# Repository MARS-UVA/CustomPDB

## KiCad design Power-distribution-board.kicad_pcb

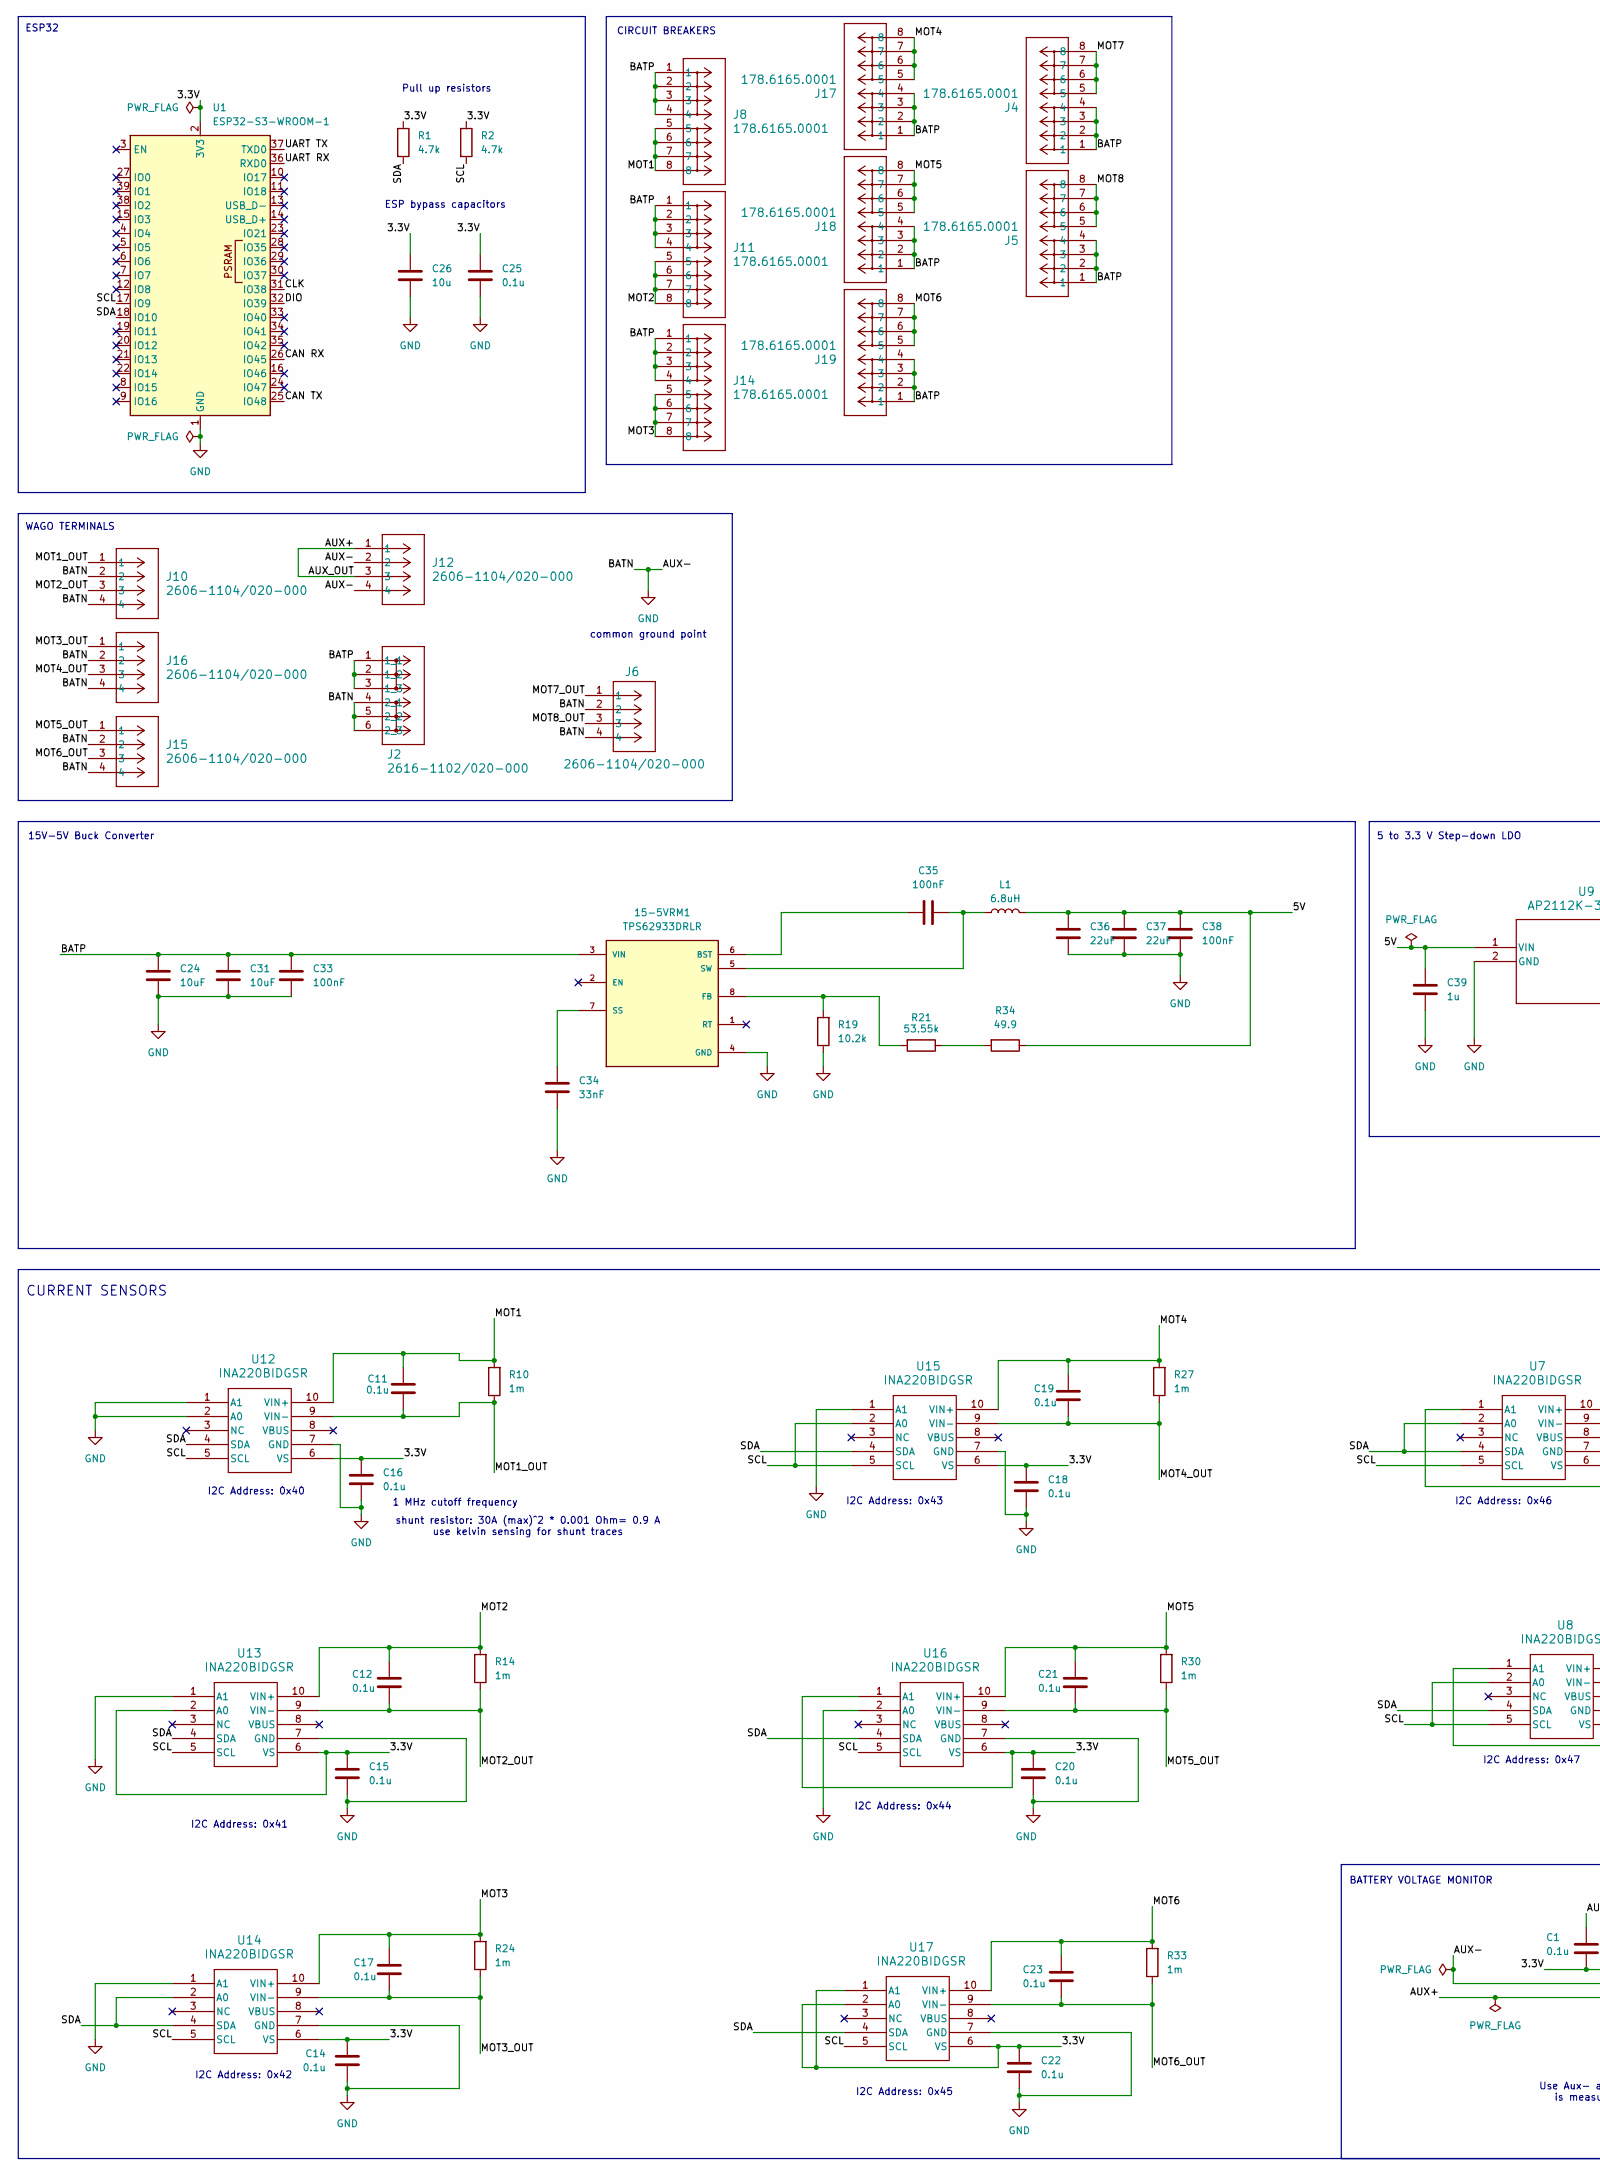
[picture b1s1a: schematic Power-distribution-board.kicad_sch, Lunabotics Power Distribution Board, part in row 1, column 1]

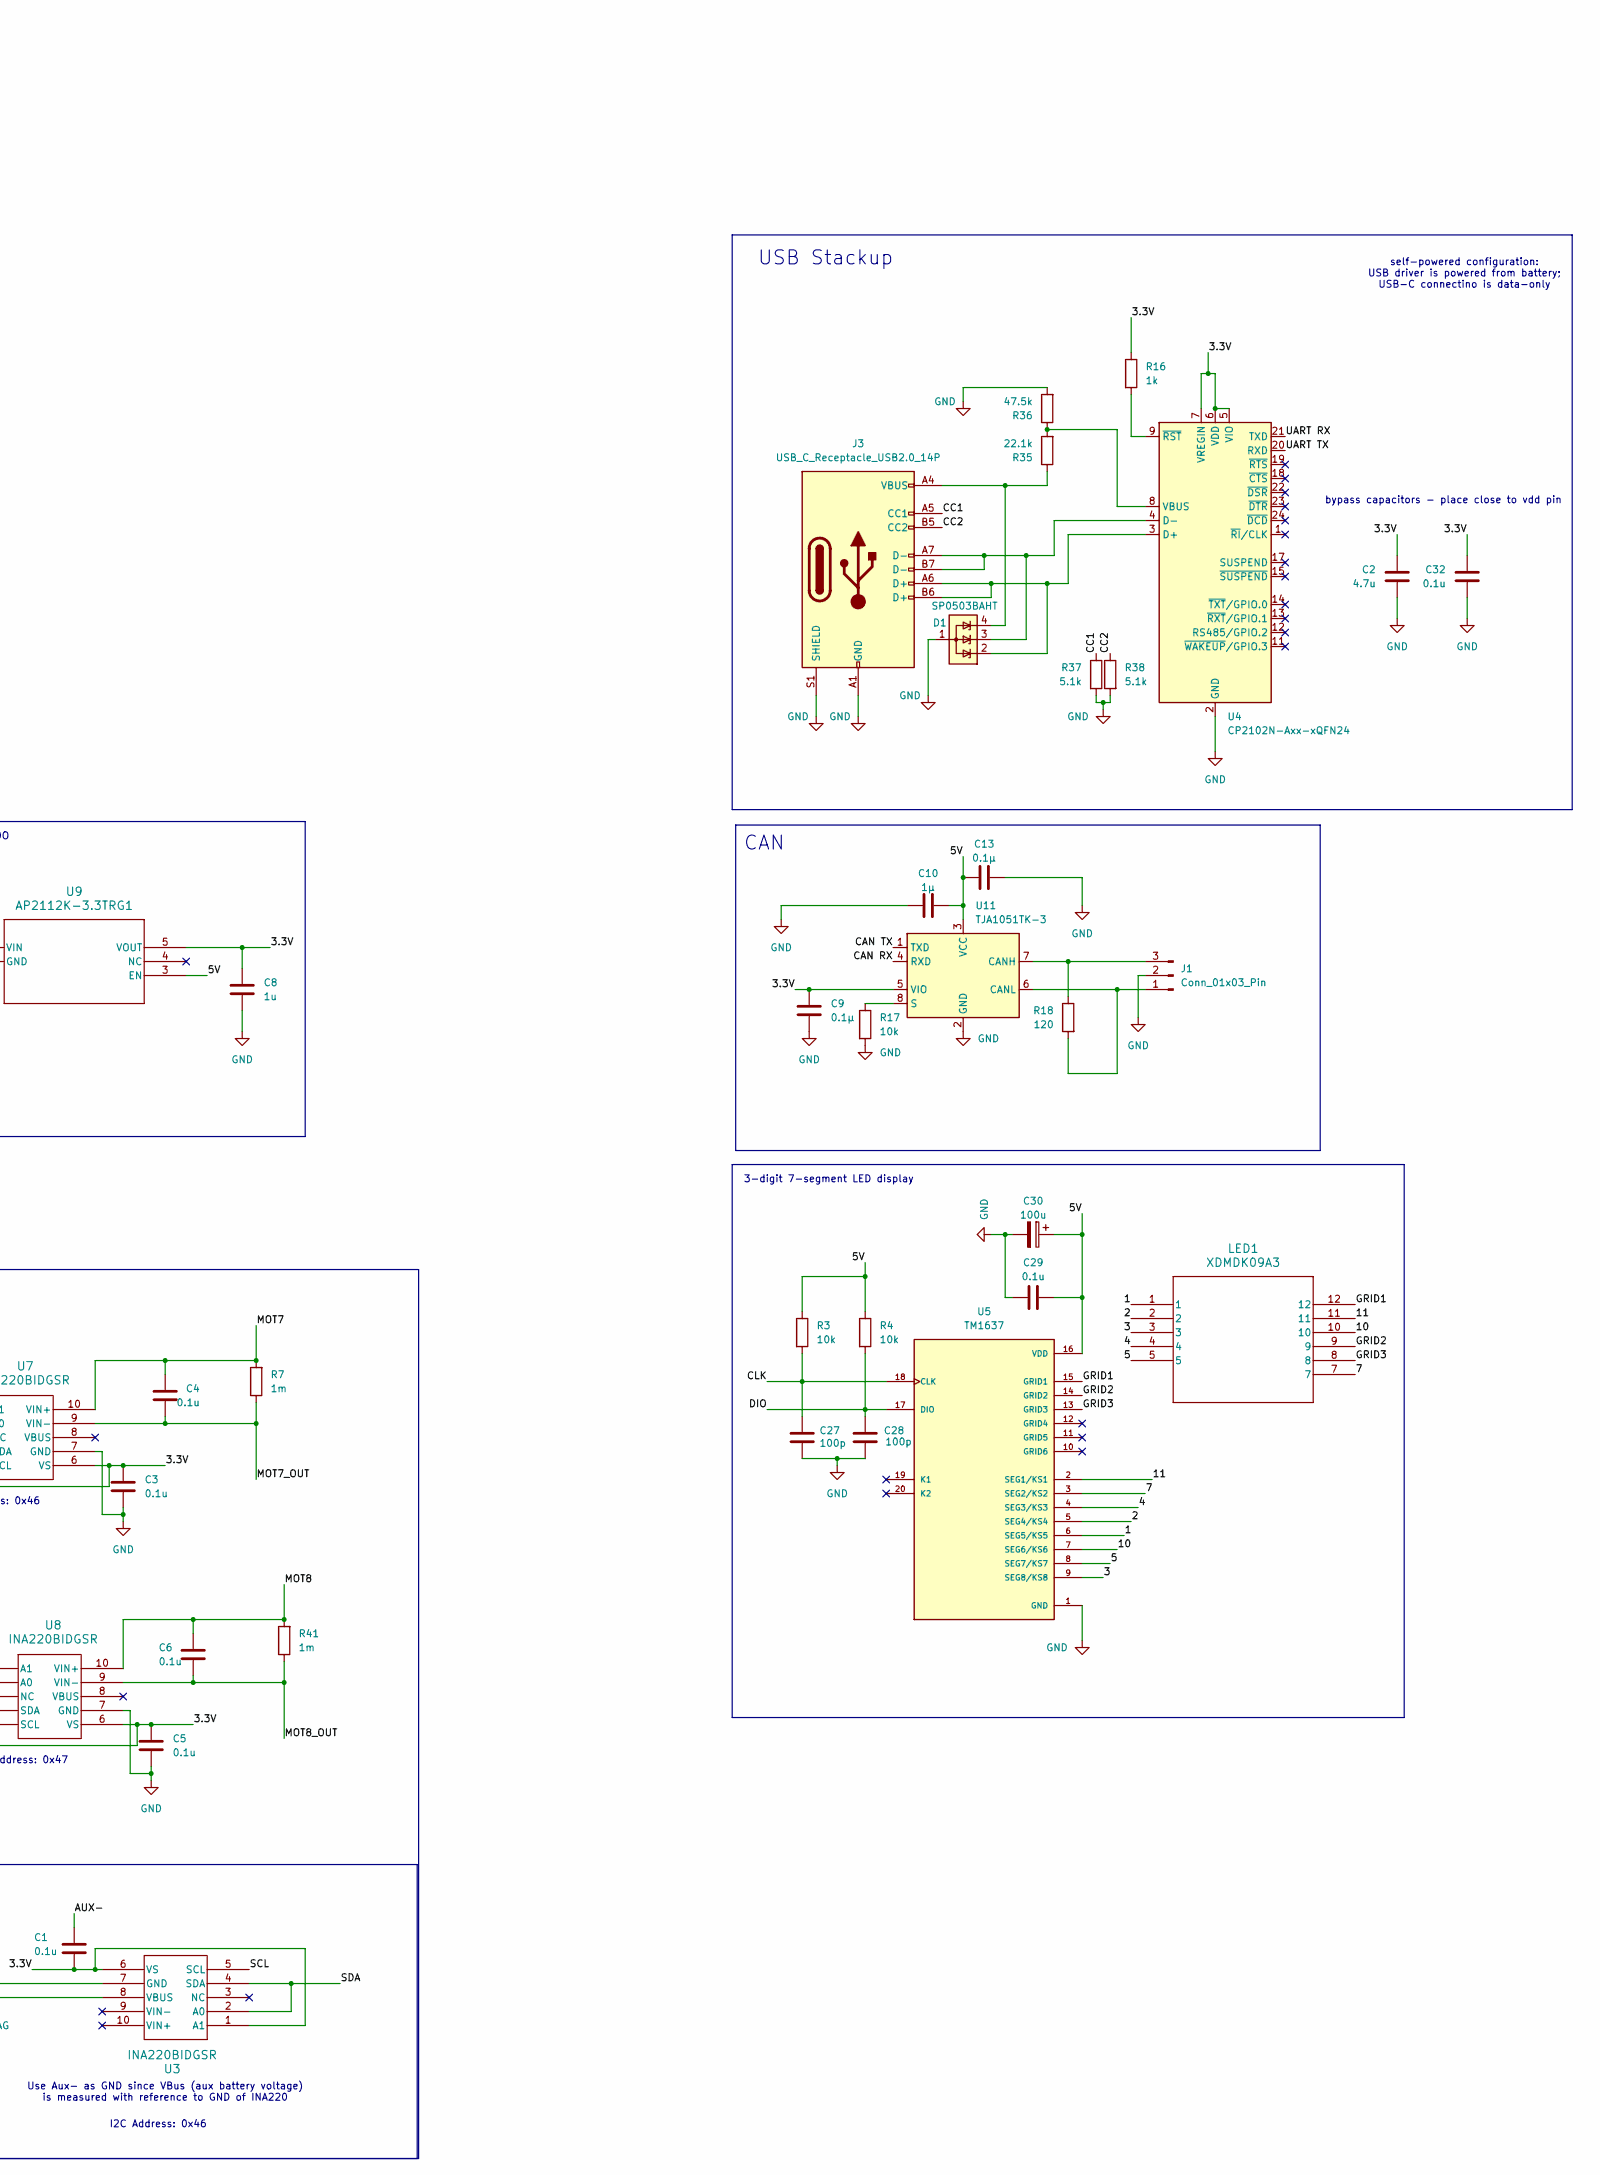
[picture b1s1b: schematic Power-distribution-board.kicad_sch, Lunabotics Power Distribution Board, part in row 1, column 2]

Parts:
15-5VRM1: TPS62933DRLR; SOT-5X3-8_DRL_TEX; PARTREV D
C1, C3, C4, C5, C6, C11, C12, C14, C15, C16, C17, C18, C19, C20, C21, C22, C23, C25, C29, C32: 0.1u; R_0805_2012Metric
C2: 4.7u; C_0805_2012Metric
C8, C39: 1u; C_0805_2012Metric
C9, C13: 0.1µ; C_0805_2012Metric
C10: 1µ; C_0805_2012Metric
C24, C31: 10uF; CAP_CGA5_TDK-M
C26: 10u; C_0805_2012Metric
C27, C28: 100p; C_0805_2012Metric
C30: 100u; CP_Elec_3x5.4
C33, C35, C38: 100nF; C_0805_2012Metric
C34: 33nF; C_0805_2012Metric
C36, C37: 22uF; C_0805_2012Metric
D1: SP0503BAHT; SOT-143
J1: Conn_01x03_Pin; Molex_Micro-Fit_3.0_43650-0300_1x03_P3.00mm_Horizontal
J2: 2616-1102/020-000; CONN2_2616-1102&slash_020-000_WAG
J3: USB_C_Receptacle_USB2.0_14P; USB_C_Receptacle_HRO_TYPE-C-31-M-12
J4, J5, J8, J11, J14, J17, J18, J19: 178.6165.0001; CONN_178.6165.0001_LTF
J6, J10, J12, J15, J16: 2606-1104/020-000; CONN4_2606-1104&slash_020-000_WAG
L1: 6.8uH; L_Wuerth_XHMI-6060
LED1: XDMDK09A3; XDMDK09A3_SLD
R1, R2: 4.7k; R_0402_1005Metric
R3, R4, R17: 10k; R_0402_1005Metric
R7, R10, R14, R24, R27, R30, R33, R41: 1m; RES_3920R_1L00x_BRN-M
R16: 1k; R_0402_1005Metric
R18: 120; R_0402_1005Metric
R19: 10.2k; R_0805_2012Metric
R21: 53.55k; R_0805_2012Metric
R34: 49.9; R_0805_2012Metric
R35: 22.1k; R_0402_1005Metric
R36: 47.5k; R_0402_1005Metric
R37, R38: 5.1k; R_0402_1005Metric
U1: ESP32-S3-WROOM-1
U3, U7, U8, U12, U13, U14, U15, U16, U17: INA220BIDGSR; DGS10
U4: CP2102N-Axx-xQFN24; QFN-24-1EP_4x4mm_P0.5mm_EP2.6x2.6mm
U5: TM1637; LED_driver_DIP778W43P254L2612H431Q20N; PARTREV v2.5
U9: AP2112K-3.3TRG1; SOT_RG1_DIO
U11: TJA1051TK-3; HVSON-8-1EP_3x3mm_P0.65mm_EP1.6x2.4mm

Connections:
/1: LED1.1, U5.6 (SEG5/KS5)
/2: LED1.2, U5.5 (SEG4/KS4)
/3: LED1.3, U5.9 (SEG8/KS8)
/3.3V: C1.1, C2.2, C3.1, C5.1, C8.1, C9.2, C14.1, C15.1, C16.1, C18.1, C20.1, C22.1, C25.2, C26.2, C32.2, R1.1, R2.1, R16.1, U1.2 (3V3), U3.1 (A1), U3.6 (VS), U4.5 (VIO), U4.6 (VDD), U4.7 (VREGIN), U7.1 (A1), U7.6 (VS), U8.1 (A1), U8.6 (VS), U9.5 (VOUT), U11.5 (VIO), U12.6 (VS), U13.2 (A0), U13.6 (VS), U14.6 (VS), U15.6 (VS), U16.1 (A1), U16.6 (VS), U17.1 (A1), U17.2 (A0), U17.6 (VS)
/4: LED1.4, U5.4 (SEG3/KS3)
/5: LED1.5, U5.8 (SEG7/KS7)
/5V: C10.2, C13.1, C29.2, C30.1, C36.1, C37.1, C38.1, C39.1, L1.2, R3.1, R4.1, R34.1, U5.16 (VDD), U9.1 (VIN), U9.3 (EN), U11.3 (VCC)
/7: LED1.7, U5.3 (SEG2/KS2)
/10: LED1.10, U5.7 (SEG6/KS6)
/11: LED1.11, U5.2 (SEG1/KS1)
/AUX+: J12.1, J12.3, U3.8 (VBUS)
/BATP: 15-5VRM1.3 (VIN), C24.1, C31.1, C33.1, J2.1 (1_1), J2.2 (1_2), J2.3 (1_3), J4.1, J4.2, J4.3, J4.4, J5.1, J5.2, J5.3, J5.4, J8.1, J8.2, J8.3, J8.4, J11.1, J11.2, J11.3, J11.4, J14.1, J14.2, J14.3, J14.4, J17.1, J17.2, J17.3, J17.4, J18.1, J18.2, J18.3, J18.4, J19.1, J19.2, J19.3, J19.4
/CAN RX: U1.26 (IO45), U11.4 (RXD)
/CAN TX: U1.25 (IO48), U11.1 (TXD)
/CC1: J3.A5 (CC1), R37.1
/CC2: J3.B5 (CC2), R38.1
/CLK: C27.2, R3.2, U1.31 (IO38), U5.18 (CLK)
/DIO: C28.1, R4.2, U1.32 (IO39), U5.17 (DIO)
/GRID1: LED1.12, U5.15 (GRID1)
/GRID2: LED1.9, U5.14 (GRID2)
/GRID3: LED1.8, U5.13 (GRID3)
/MOT1: C11.1, J8.5, J8.6, J8.7, J8.8, R10.2, U12.10 (VIN+)
/MOT1_OUT: C11.2, J10.1, R10.1, U12.9 (VIN-)
/MOT2: C12.1, J11.5, J11.6, J11.7, J11.8, R14.2, U13.10 (VIN+)
/MOT2_OUT: C12.2, J10.3, R14.1, U13.9 (VIN-)
/MOT3: C17.1, J14.5, J14.6, J14.7, J14.8, R24.2, U14.10 (VIN+)
/MOT3_OUT: C17.2, J16.1, R24.1, U14.9 (VIN-)
/MOT4: C19.1, J17.5, J17.6, J17.7, J17.8, R27.2, U15.10 (VIN+)
/MOT4_OUT: C19.2, J16.3, R27.1, U15.9 (VIN-)
/MOT5: C21.1, J18.5, J18.6, J18.7, J18.8, R30.2, U16.10 (VIN+)
/MOT5_OUT: C21.2, J15.1, R30.1, U16.9 (VIN-)
/MOT6: C23.1, J19.5, J19.6, J19.7, J19.8, R33.2, U17.10 (VIN+)
/MOT6_OUT: C23.2, J15.3, R33.1, U17.9 (VIN-)
/MOT7: C4.1, J4.5, J4.6, J4.7, J4.8, R7.2, U7.10 (VIN+)
/MOT7_OUT: C4.2, J6.1, R7.1, U7.9 (VIN-)
/MOT8: C6.1, J5.5, J5.6, J5.7, J5.8, R41.2, U8.10 (VIN+)
/MOT8_OUT: C6.2, J6.3, R41.1, U8.9 (VIN-)
/SCL: R2.2, U1.17 (IO9), U3.5 (SCL), U7.5 (SCL), U8.2 (A0), U8.5 (SCL), U12.5 (SCL), U13.5 (SCL), U14.5 (SCL), U15.2 (A0), U15.5 (SCL), U16.5 (SCL), U17.5 (SCL)
/SDA: R1.2, U1.18 (IO10), U3.2 (A0), U3.4 (SDA), U7.2 (A0), U7.4 (SDA), U8.4 (SDA), U12.4 (SDA), U13.4 (SDA), U14.2 (A0), U14.4 (SDA), U15.4 (SDA), U16.4 (SDA), U17.4 (SDA)
/UART RX: U1.36 (RXD0), U4.21 (TXD)
/UART TX: U1.37 (TXD0), U4.20 (RXD)
GND: 15-5VRM1.4 (GND), C1.2, C2.1, C3.2, C5.2, C8.2, C9.1, C10.1, C13.2, C14.2, C15.2, C16.2, C18.2, C20.2, C22.2, C24.2, C25.1, C26.1, C27.1, C28.2, C29.1, C30.2, C31.2, C32.1, C33.2, C34.2, C36.2, C37.2, C38.2, C39.2, D1.1 (A), J1.2, J2.4 (2_1), J2.5 (2_2), J2.6 (2_3), J3.A1 (GND), J3.A12 (GND), J3.B1 (GND), J3.B12 (GND), J3.S1 (SHIELD), J6.2, J6.4, J10.2, J10.4, J12.2, J12.4, J15.2, J15.4, J16.2, J16.4, R17.2, R19.1, R36.2, R37.2, R38.2, U1.1 (GND), U1.40 (GND), U1.41 (GND), U3.7 (GND), U4.2 (GND), U4.25 (GND), U5.1 (GND), U7.7 (GND), U8.7 (GND), U9.2 (GND), U11.2 (GND), U11.9 (GND), U12.1 (A1), U12.2 (A0), U12.7 (GND), U13.1 (A1), U13.7 (GND), U14.1 (A1), U14.7 (GND), U15.1 (A1), U15.7 (GND), U16.2 (A0), U16.7 (GND), U17.7 (GND)
unnamed: 15-5VRM1.6 (BST), C35.2
unnamed: 15-5VRM1.8 (FB), R19.2, R21.2
unnamed: 15-5VRM1.7 (SS), C34.1
unnamed: 15-5VRM1.5 (SW), C35.1, L1.1
unnamed: D1.4 (K), J3.A4 (VBUS), J3.A9 (VBUS), J3.B4 (VBUS), J3.B9 (VBUS), R35.1
unnamed: R21.1, R34.2
unnamed: D1.2 (K), J3.A6 (D+), J3.B6 (D+), U4.3 (D+)
unnamed: D1.3 (K), J3.A7 (D-), J3.B7 (D-), U4.4 (D-)
unnamed: R35.2, R36.1, U4.8 (VBUS)
unnamed: R16.2, U4.9 (~RST)
unnamed: R17.1, U11.8 (S)

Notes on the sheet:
ESP bypass capacitors
I2C Address: 0x45
shunt resistor: 30A (max)^2 * 0.001 Ohm= 0.9 A use kelvin sensing for shunt traces
3-digit 7-segment LED display
bypass capacitors - place close to vdd pin
I2C Address: 0x41
I2C Address: 0x44
1 MHz cutoff frequency
Pull up resistors
15V-5V Buck Converter
I2C Address: 0x42
ESP32
I2C Address: 0x46
BATTERY VOLTAGE MONITOR
CAN
self-powered configuration: USB driver is powered from battery; USB-C connectino is data-only
I2C Address: 0x43
WAGO TERMINALS
5 to 3.3 V Step-down LDO
CURRENT SENSORS
I2C Address: 0x40
CIRCUIT BREAKERS
I2C Address: 0x47
USB Stackup
I2C Address: 0x46
common ground point
Use Aux- as GND since VBus (aux battery voltage) is measured with reference to GND of INA220

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
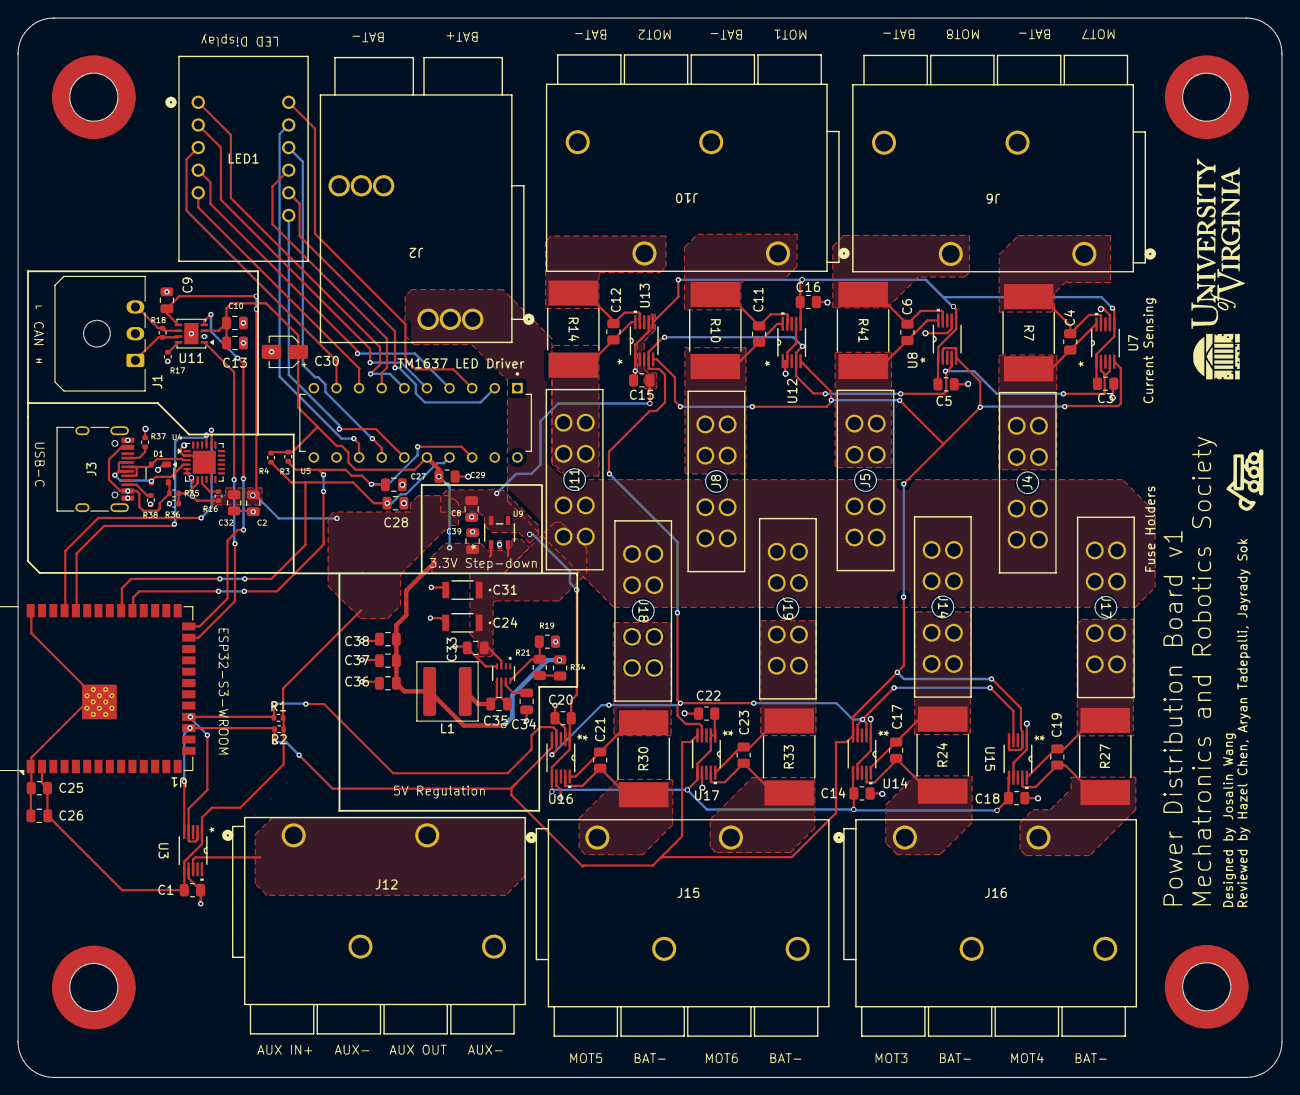
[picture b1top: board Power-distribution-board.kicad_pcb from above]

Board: 2 copper layers, 142.0 x 119.0 mm, 94 parts (0 on the bottom side), 55 nets.

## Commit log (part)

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2026-03-10 schematic of buck converter 15v to 5v for esp
2026-03-15 Add files via upload
    First steps, batteries, buck converter unfinished
2026-03-20 add current sensors and CAN
    still left to complete: battery voltage, aux battery circuit, esp
2026-04-07 FINISHED schematic
2026-04-10 Create project files
2026-04-10 Created KiCad Project
2026-04-10 Revert "Create project files"
    This reverts commit bf36d6aff1839375a85b6a2cefe588a7d128445d.
2026-04-10 Updated connectors and started resistor values
2026-04-27 Update INA220 circuit
2026-04-28 Finalize INA220 circuits
2026-04-28 changed 15-5v buck converter and fix current sensors
2026-04-28 Finalize schematics
2026-05-01 Changed breaker labels and added all footprints
2026-05-01 fixed footprints error, begun pcb design
    added footprints into project and started pcb design
2026-06-19 work on pcb editor
    changed layout of components, changed to 4 layer pcb, set minimum trace width 0.2mm
2026-06-19 set layout
2026-06-21 update layout
    added board edge and planes
2026-06-21 rearrangement
2026-06-28 added 4-digit display & pwr planes
    add 4digit led and tm1637 driver
2026-06-28 added 15vin pwr plane cus i forgot
